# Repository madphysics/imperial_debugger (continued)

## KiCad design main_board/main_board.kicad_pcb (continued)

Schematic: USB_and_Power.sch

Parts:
C1, C3, C6, C8: 4.7uF; C_1206_3216Metric_Pad1.39x1.80mm_HandSolder
C2, C4, C5, C7, C9: 0.1uF; C_0603_1608Metric_Pad0.99x1.00mm_HandSolder
J1: USB_B_Micro; USB_Micro-B_Molex-105017-0001
L1, L2, L3: 600R/0.6A; L_0805_2012Metric_Pad1.29x1.40mm_HandSolder
R1, R6: 0R; R_0603_1608Metric_Pad0.99x1.00mm_HandSolder
R2, R3: 10R; R_0603_1608Metric_Pad0.99x1.00mm_HandSolder
R4: 100K; R_0603_1608Metric_Pad0.99x1.00mm_HandSolder
R5: 150K; R_0603_1608Metric_Pad0.99x1.00mm_HandSolder
TP1: Test_Point; TestPoint_Loop_D2.60mm_Drill1.6mm_Beaded
TP2, TP3, TP4, TP5: Test_Point; TestPoint_Pad_D2.0mm
U1: MIC5504-3.3YM5; SOT-23-5
U2: USBLC6-2SC6; SOT-23-6

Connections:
/USB_and_Power/USB_N: J1.2 (D-), U2.1
/USB_and_Power/USB_P: J1.3 (D+), U2.3
D_N: R3.2; also elsewhere on the board
D_P: R2.2; also elsewhere on the board
GND: C1.2, C2.2, C3.2, C4.2, C5.2, C6.2, C7.2, C8.2, C9.2, J1.5 (GND), R1.2, R5.2, TP1.1, U1.2, U2.2; also elsewhere on the board
unnamed: C5.1, J1.1 (VBUS), L1.2, U2.5
unnamed: J1.6 (Shield), R1.1
unnamed: R2.1, U2.4
unnamed: R3.1, U2.6
unnamed: R4.2, R5.1, R6.2
RESET#: R6.1; also elsewhere on the board
VBUS: C1.1, C2.1, L1.1, R4.1, TP2.1, U1.1, U1.3
VCC3V3: C3.1, C4.1, L2.2, L3.2, TP4.1, U1.5; also elsewhere on the board
VPHY: C6.1, C7.1, L2.1, TP3.1; also elsewhere on the board
VPLL: C8.1, C9.1, L3.1, TP5.1; also elsewhere on the board

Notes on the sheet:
Ground Clip
Outputs from Block

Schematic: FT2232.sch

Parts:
C10, C13, C14, C16, C17, C18, C19, C20, C21, C22: 0.1uF; C_0603_1608Metric_Pad0.99x1.00mm_HandSolder
C11: 4.7uF; C_1206_3216Metric_Pad1.39x1.80mm_HandSolder
C12, C15: 30pF; C_0603_1608Metric_Pad0.99x1.00mm_HandSolder
D1, D2: LED; LED_1206_3216Metric_Pad1.22x1.80mm_HandSolder
J2, J3: Conn_02x13_Odd_Even; PinHeader_2x13_P2.00mm_Horizontal
Q1, Q2: DMP2170; SOT-23
R7, R13, R15: 10K; R_0603_1608Metric_Pad0.99x1.00mm_HandSolder
R8: 2K; R_0603_1608Metric_Pad0.99x1.00mm_HandSolder
R9: 12K/1%; R_0603_1608Metric_Pad0.99x1.00mm_HandSolder
R10: 0R; R_0603_1608Metric_Pad0.99x1.00mm_HandSolder
R11, R12: 4.7K; R_0603_1608Metric_Pad0.99x1.00mm_HandSolder
R14, R16: 330R; R_0603_1608Metric_Pad0.99x1.00mm_HandSolder
R17, R18, R19, R20: 4.7K; R_0603_1608Metric_Pad1.05x0.95mm_HandSolder
TP6, TP7: Test_Point; TestPoint_Pad_D2.0mm
U3: 93LC56B; SOIC-8_3.9x4.9mm_P1.27mm
U4: FT2232H; LQFP-64_10x10mm_P0.5mm
Y1: 12MHz; Crystal_SMD_Abracon_ABM3-2Pin_5.0x3.2mm_HandSoldering

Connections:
/USB_Bridge/VCORE: C11.1, C13.1, C14.1, C16.1, C17.1, C18.1, TP6.1, U4.12, U4.37, U4.49, U4.64
AC0: J2.21, U4.26
AC1: J2.22, U4.27
AC2: J2.19, U4.28
AC3: J2.20, U4.29
AC4: J2.17, R17.2, U4.30
AC5: J2.18, R18.2, U4.32
AC6: J2.15, R19.2, U4.33
AC7: J2.16, R20.2, U4.34
AD0: J2.25, U4.16
AD1: J2.26, U4.17
AD2: J2.24, U4.18
BC0: J3.17, U4.48
BC1: J3.18, U4.52
BC2: J3.15, U4.53
BC3: J3.16, U4.54
BC4: J3.11, U4.55
BC5: J3.12, U4.57
BC6: J3.9, U4.58
BC7: J3.10, U4.59
BD0: J3.25, U4.38
BD1: J3.26, U4.39
BD2: J3.23, U4.40
BD3: J3.24, U4.41
BD4: J3.21, U4.43
BD5: J3.22, U4.44
BD6: J3.19, U4.45
BD7: J3.20, U4.46
CFGOUT: J2.12, U4.19
CFGRST: J2.11, U4.21
D_N: U4.7; also elsewhere on the board
D_P: U4.8; also elsewhere on the board
GND: C10.2, C11.2, C12.2, C13.2, C14.2, C15.2, C16.2, C17.2, C18.2, C19.2, C20.2, C21.2, C22.2, J2.3, J2.4, J2.7, J2.8, J2.13, J2.14, J3.3, J3.4, J3.7, J3.8, J3.13, J3.14, Q1.3, Q2.3, R9.2, U3.5 (GND), U4.1, U4.5, U4.10, U4.11, U4.13, U4.15, U4.25, U4.35, U4.47, U4.51; also elsewhere on the board
unnamed: C12.1, U4.2, Y1.2
unnamed: C15.1, U4.3, Y1.1
unnamed: D1.1 (K), R14.1
unnamed: D2.1 (K), R16.1
unnamed: Q1.1, R13.2, U4.60
unnamed: Q1.2, R14.2
unnamed: Q2.1, R15.2, U4.36
unnamed: Q2.2, R16.2
unnamed: R7.2, R8.2, U3.4 (DO)
unnamed: R8.1, U3.3 (DI), U4.61
unnamed: R9.1, U4.6
unnamed: U3.1 (CS), U4.63
unnamed: U3.2 (SCLK), U4.62
RESET#: U4.14; also elsewhere on the board
SCL: J2.10, R11.1, U4.22
SDA: J2.9, R12.1, U4.23, U4.24
VCC3V3: C10.1, J2.5, J2.6, J3.5, J3.6, R10.2, U4.50; also elsewhere on the board
VIO: C19.1, C20.1, C21.1, C22.1, D1.2 (A), D2.2 (A), J2.1, J2.2, J3.1, J3.2, R7.1, R10.1, R11.2, R12.2, R13.1, R15.1, R17.1, R18.1, R19.1, R20.1, TP7.1, U3.8 (VCC), U4.20, U4.31, U4.42, U4.56
VPHY: U4.4; also elsewhere on the board
VPLL: U4.9; also elsewhere on the board

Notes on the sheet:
Place Close to pins

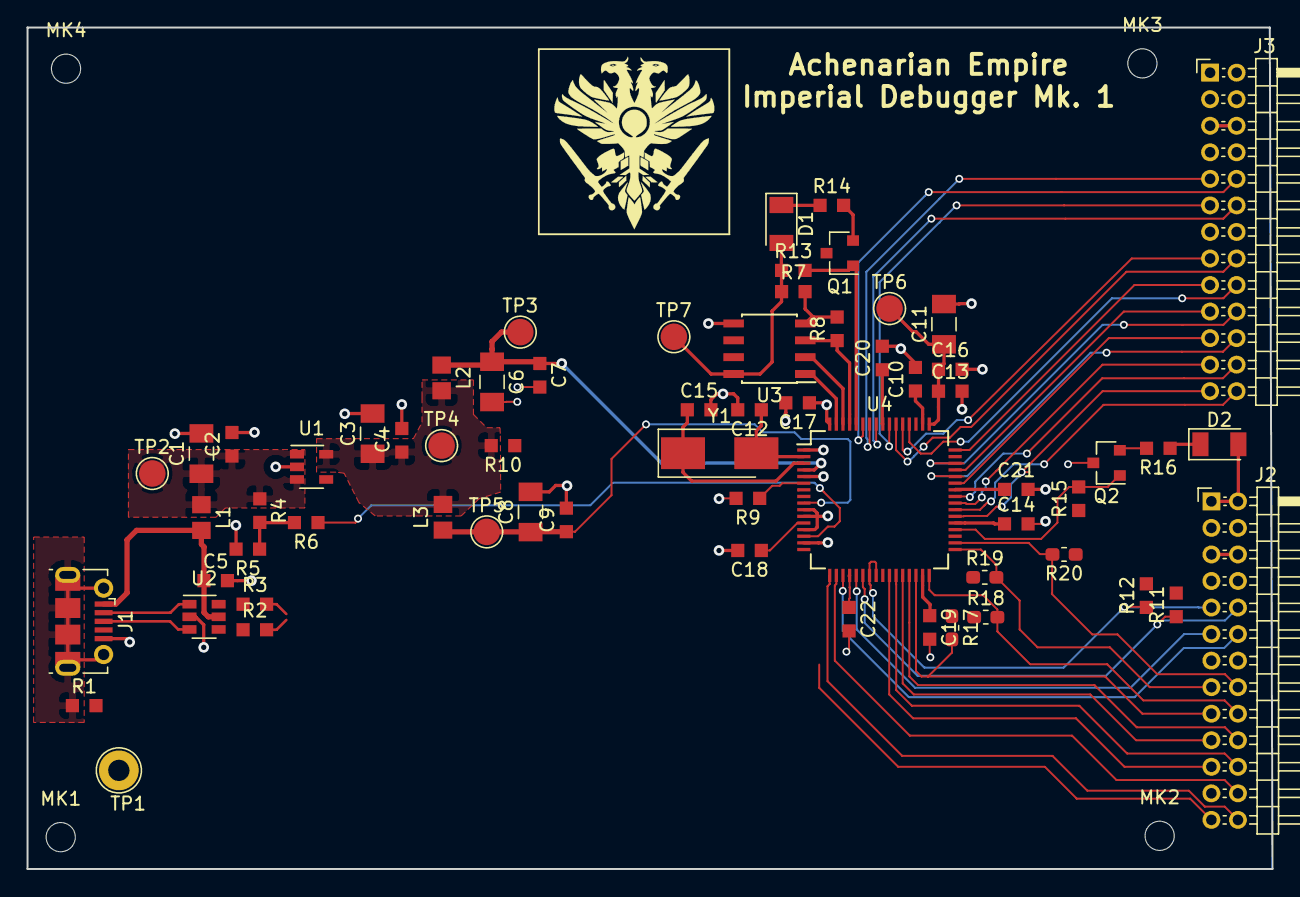
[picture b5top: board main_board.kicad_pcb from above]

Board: 2 copper layers, 93.8 x 63.4 mm, 68 parts (0 on the bottom side), 61 nets.

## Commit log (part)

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2018-05-15 Initial
2018-05-15 Simple Readme
2018-05-17 Added more docs and a pic of the config mechanism idea.
2018-05-17 Little changes to the wording.
2018-05-17 Found another mux chip..
2018-05-20 Added some more notes
2018-05-20 Data sheets and updated auto config diagram
    A selection of data sheets and app notes.
2018-05-20 More data sheets, plus LT Spice sim and model for led mosfet.
2018-05-20 Updated to ignore html readme. .md version is fine
2018-05-21 Adding design files.
    Schematic and layout starting.
    Some more data sheets being added.
2018-05-21 Added the cache.lib file
2019-06-22 Updates when doing some layout testing
2019-06-22 Backlink to CADLAB.io has been added.
2021-08-21 Cleaning up.
    Going to do a new design.
2021-08-21 Updated the README
2021-08-21 Remove old gfx
2021-08-21 Some more ideas added
2021-08-22 Adding in first few pages and some data sheets
2021-08-22 Project, pcb and lib
2021-08-22 USB and FTDI chip
2021-08-22 Remove wrong cache
2021-09-05 Updated with the ttl output
    Adding a lot of footprints and other bits.
    Changed TVS on USB
    Added fuse on USB 5V
    TTL level translators, 2x. Go from 3v3 to 1v8, then "anything" to 1v8
    for the output.
    2x LDO for 3v3->1v8, 3v3->2v5
2021-09-19 Adding some LED stuff.
2021-09-19 Added some footprints and started to look at layout
2021-11-28 Updates as we do routing.
    Changed discrete jumpres to a 2x4 block and 2x3 block, 2mm pitch.
    Started routing each tranciever block
2021-12-03 Almost fully routed.. lots of DRC's to sort out.
    Also need to get correct pcb parameters to do more checks.
2022-01-08 Updates with all the routing and moving to kicad 6.0
2022-01-08 Remove kicad 5.x files.
2025-09-14 After update to kicak 9.0
2025-09-14 Add backupfiles to ignore
2025-09-17 Updated to remove the level shifters
    Just have 3v3 ttl outputs for now, trancievers will be on different
    boards
2025-12-30 Updated power leds and external protection on Serial
2026-02-07 Updated with the new design.
    Removed all level translators.
    4 sockets, 2x6 pin outputs
    New PCB shape and routing
2026-02-07 Quick Readme update
2026-02-15 Add some info to the master document
2026-02-15 Add initial new submodule
    Created from our new project template.
2026-02-17 Updated Schematic and PCB for first pass at the design
2026-03-08 Add rs485/422 module
    Has a custom 2x6 pin connector in a local library
2026-03-08 Quick update to the ttl module board layout
2026-03-08 Add rs232 module
2026-03-08 Add the updated pin socket to the local library on the ttl submodule
2026-03-28 Update schematics after moving to KiCad 10
    Added some footprints to a local lib, as the silkscreen caused issues.
2026-03-28 Update Ignore
2026-04-12 Update USB routing
2026-05-16 Sorting out BOMs
